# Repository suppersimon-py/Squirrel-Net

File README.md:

<div align="center">

  <h2>Squirrel-Core</h2>
  <h2>NOT FINISHED</h2>
  <p>
    <strong>SquirrelCore</strong> is an open-source PCB built around the <strong>ESP32-S3</strong> and <strong>SX1262</strong>.
    It is designed for long-range mesh networking using the open-source 
    <a href="https://meshtastic.org" target="_blank" rel="noopener noreferrer">Meshtastic</a> firmware.
    It can function as a client, node, or repeater in a distributed network.
  </p>
</div>

  <p>
    I wanted to design this as a challenge and a learning expirence on radio circuity for some time now, but without the funding (I'm kinda broke rn) this idea of mine wouldn't come to reality.
  </p>
  <h3>Continuing the development process</h3>
  <p>
    My plans are to not just stop on the PCB design but to also design a case around it. I am a visual modeler, I can't start work on the case until i have it in hand and can mesure and test fit,
    But I can assure I do have intresting design ideas for it. 
  </p>
  <p>
    Currently I have a github workflow that will automatically update, build, and release new versions of the meshtaic firmware to the realses page.
  </p>
  <p>
    I also need to fix somethings and test the actual firmware firmware.
  </p>

<div align="left">
  <h3>Features</h3>
  <ul>
    <li>ESP32-S3 microcontroller</li>
    <li>8MB Flash memory</li>
    <li>LoRaWAN, Wi-Fi, Bluetooth, and USB-C serial connectivity</li>
    <li>Adjustable battery charging: 400 mA or 1 A</li>
    <li>OLED display</li>
    <li>BME280 sensor (temperature, humidity, pressure)</li>
    <li>GPS module</li>
  </ul>
</div>

<div align="center">
  <h3>Meshtastic Links</h3>
  <p>
    <a href="https://meshtastic.org" style="text-decoration:none; font-weight:bold;">Get Started</a><br/>
    - <a href="https://meshtastic.org/docs/development/firmware/build">Building Instructions</a> – Learn how to compile the firmware from source.<br/>
    - <a href="https://meshtastic.org/docs/getting-started/flashing-firmware/esp32/">Flashing Instructions</a> – Install or update the firmware on your device.
  </p>
</div>

<div align="center">
  <h3>Licensing</h3>
</div>

<div align="left">
  <ul>
    <li>The core Meshtastic firmware in <code>/firmware/meshtastic</code> remains under its original license (as provided by the Meshtastic project).</li>
    <li>The SquirrelCore variant files in <code>/firmware/meshtastic/variants</code> are MIT-licensed (Copyright 2025 Supper Simon).</li>
    <li>When updating the repository, the variant is copied into Meshtastic, but the original Meshtastic license still applies to its code.</li>
  </ul>
</div>

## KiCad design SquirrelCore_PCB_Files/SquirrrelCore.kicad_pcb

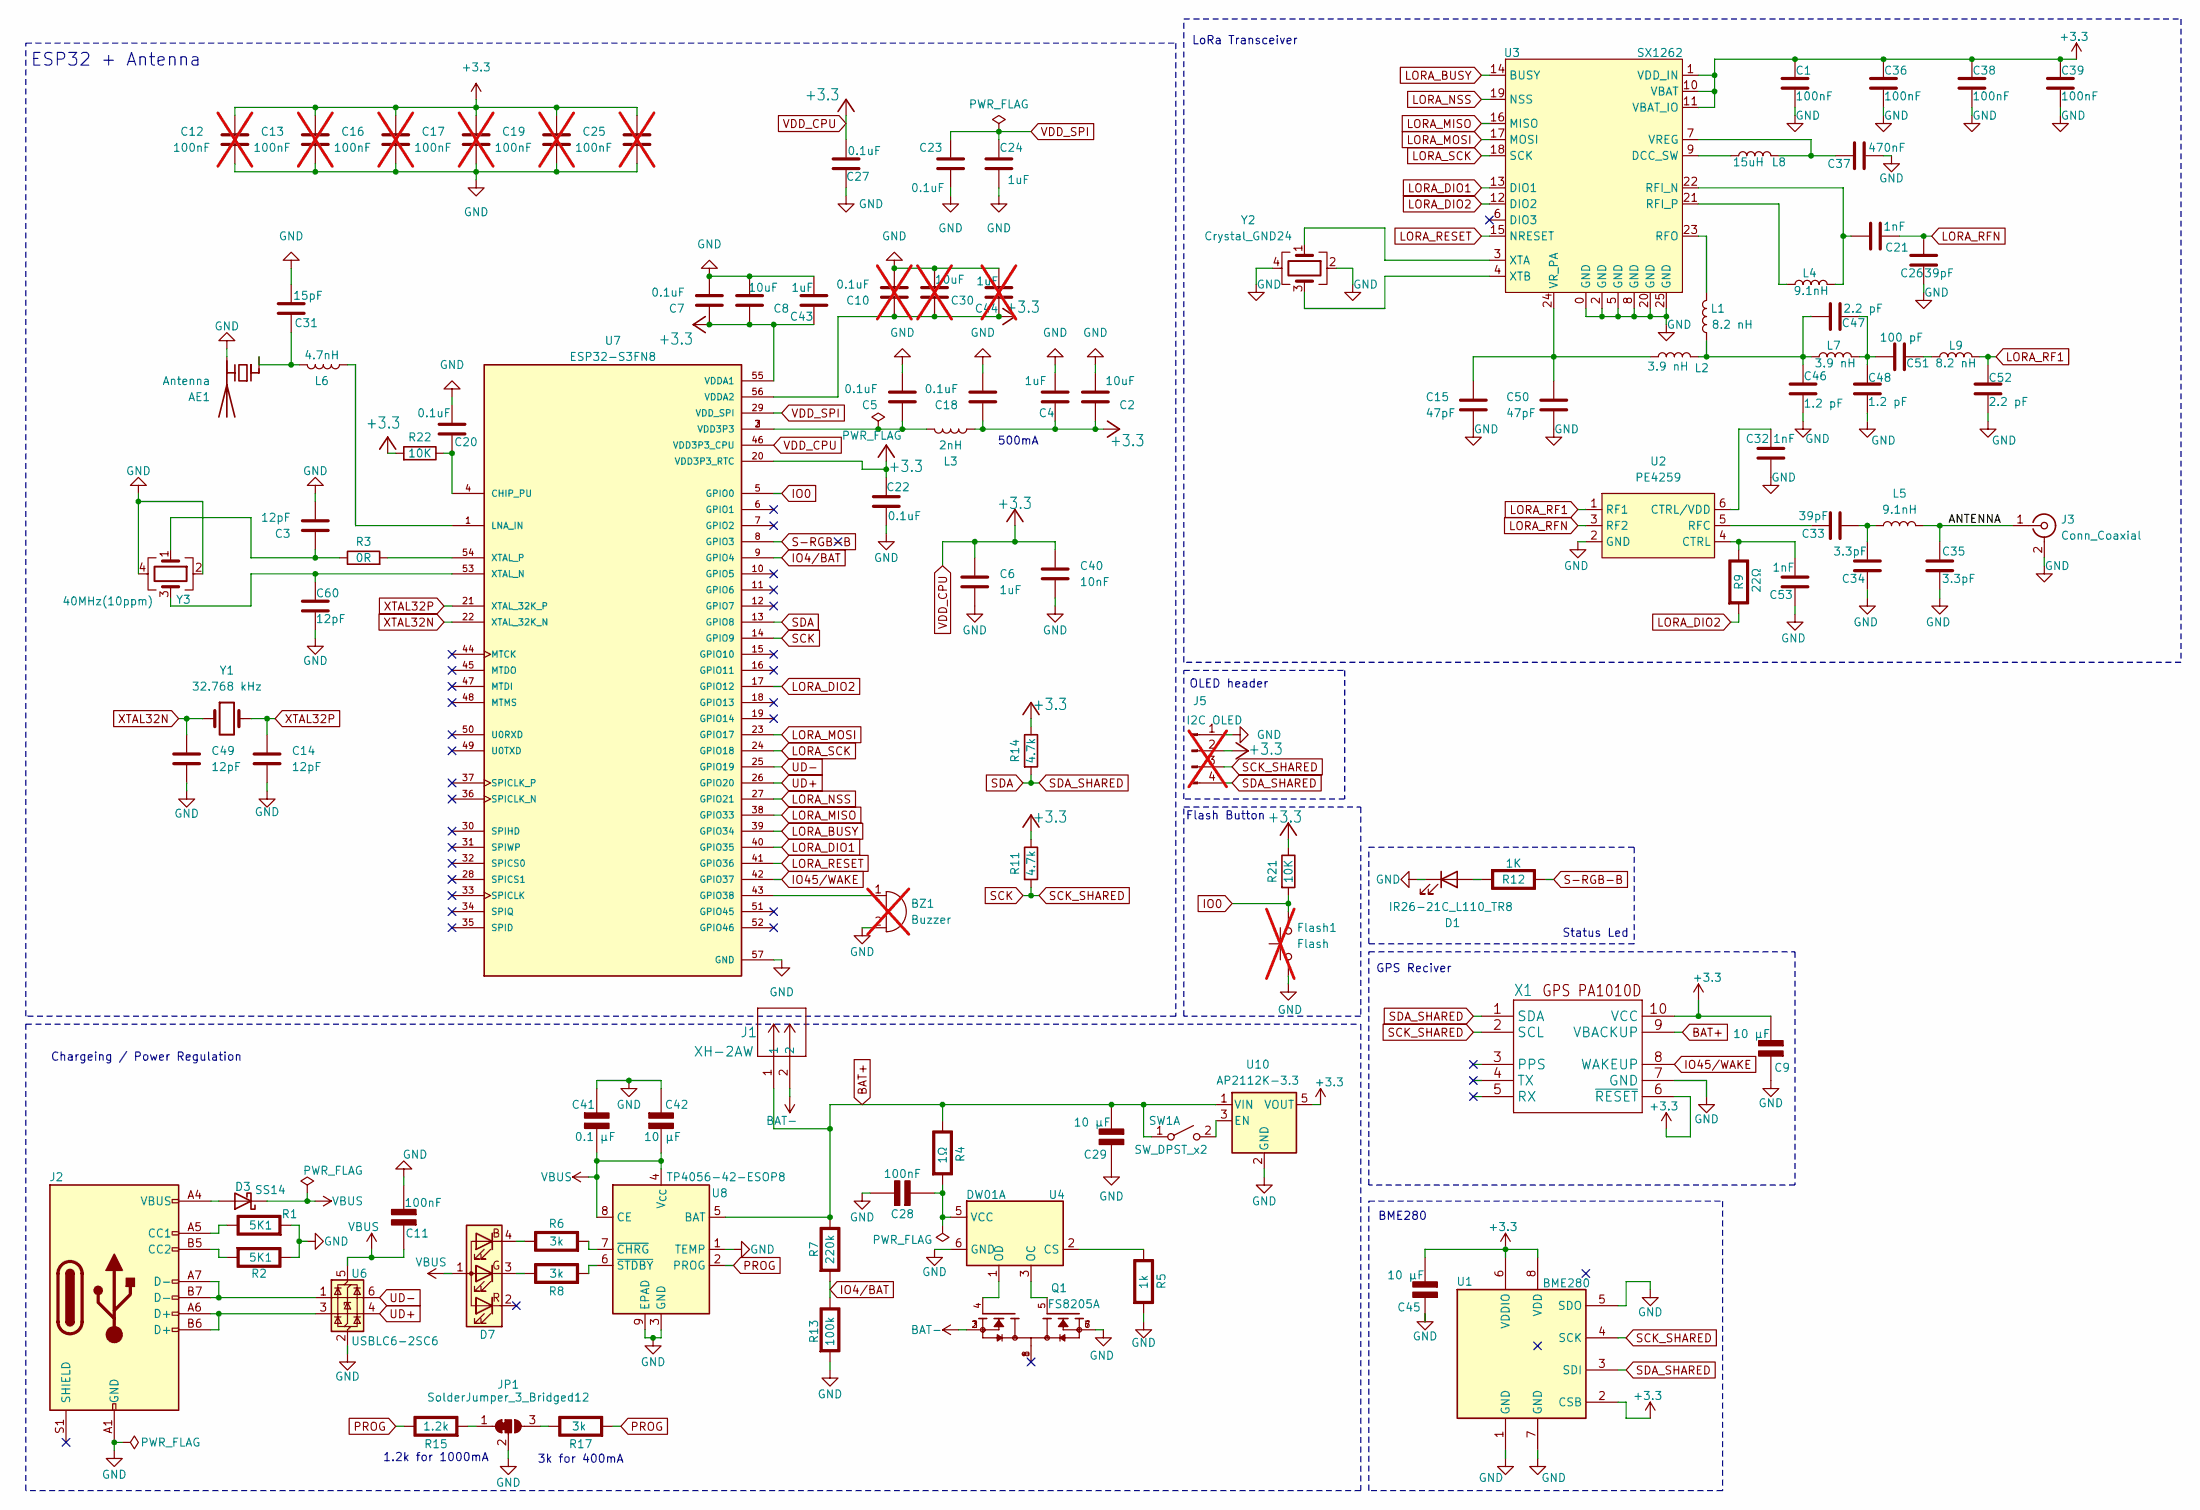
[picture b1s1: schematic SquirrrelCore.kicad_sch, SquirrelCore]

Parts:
AE1: Antenna; Texas_SWRA117D_2.4GHz_Left
BZ1: Buzzer; Buzzer_CUI_CPT-9019S-SMT; LCSC C95163; not fitted
C1, C36, C38, C39: 100nF; C_0402_1005Metric; LCSC C1525
C2, C8: 10uF; C_0402_1005Metric; MNF PART NUMBER C15525; LCSC C15525
C3, C14, C49, C60: 12pF; C_0402_1005Metric; MNF PART NUMBER C1547; LCSC C1547
C4, C6, C24, C43: 1uF; C_0402_1005Metric; MNF PART NUMBER C52923; LCSC C52923
C5, C7, C18, C20, C22, C23, C27: 0.1uF; C_0402_1005Metric; MNF PART NUMBER C1525; LCSC C1525
C9, C29, C42, C45: 10 µF; C_0402_1005Metric; Rating V; LCSC C15525
C10: 0.1uF; C_0402_1005Metric; MNF PART NUMBER C1525; LCSC C1525; not fitted
C11: 100nF; C_0402_1005Metric; Rating V; LCSC C307331
C12, C13, C16, C17, C19, C25: 100nF; C_0201_0603Metric; LCSC C49062; not fitted
C15, C50: 47pF; C_0402_1005Metric; LCSC C1567
C21: 1nF; C_0402_1005Metric; LCSC C1623
C26: 39pF; C_0402_1005Metric; LCSC C1623
C28: 100nF; C_0402_1005Metric; Rating V; LCSC C1525
C30: 10uF; C_0402_1005Metric; MNF PART NUMBER C15525; LCSC C15525; not fitted
C31: 15pF; C_0402_1005Metric; MNF PART NUMBER C1548; LCSC C1548
C32: 1nF; C_0402_1005Metric; LCSC C1523
C33: 39pF; C_0402_1005Metric; LCSC C1563
C34, C35: 3.3pF; C_0402_1005Metric; LCSC C1565
C37: 470nF; C_0402_1005Metric; LCSC C1623
C40: 10nF; C_0402_1005Metric; MNF PART NUMBER C15195; LCSC C15195
C41: 0.1 µF; C_0402_1005Metric; Rating V; LCSC C1525
C44: 1uF; C_0402_1005Metric; MNF PART NUMBER C52923; LCSC C52923; not fitted
C46, C48: 1.2 pF; C_0402_1005Metric; LCSC C1623
C47, C52: 2.2 pF; C_0402_1005Metric; LCSC C1623
C51: 100 pF; C_0402_1005Metric; LCSC C1623
C53: 1nF; C_0402_1005Metric; LCSC C1565
D1: IR26-21C_L110_TR8; LED_1206_3216Metric; LCSC C73929
D3: SS14; D_SMA; LCSC C2480
D7: LED_A_RGB; LED_RGB_Wuerth_150080M153000; LCSC C6785001
Flash1: Flash; SW_SPST_TS-1088-xR020; MNF PART NUMBER C318884; LCSC C318884; not fitted
J1: XH-2AW; CONN_XH-2AW_HRO; LCSC C157932
J2: USB_C_Receptacle_USB2.0_14P; USB_C_Receptacle_HCTL_HC-TYPE-C-16P-01A; LCSC C2894897
J3: Conn_Coaxial; IPEX-SMD_BWIPX-1-001E; LCSC C411563
J5: I2C OLED; PinHeader_1x04_P2.54mm_Vertical; LCSC C5248081; not fitted
JP1: SolderJumper_3_Bridged12; SolderJumper-3_P1.3mm_Bridged2Bar12_Pad1.0x1.5mm
L1, L9: 8.2 nH; L_0402_1005Metric; LCSC C3221788
L2, L7: 3.9 nH; L_0402_1005Metric; LCSC C3221788
L3: 2nH; L_0402_1005Metric; MNF PART NUMBER C77103; LCSC C77103
L4: 9.1nH; L_0402_1005Metric; LCSC C3221788
L5: 9.1nH; L_0402_1005Metric; LCSC C74297
L6: 4.7nH; L_0402_1005Metric; MNF PART NUMBER C13595; LCSC C13595
L8: 15uH; L_0402_1005Metric; LCSC C3221788
Q1: FS8205A; SOT-23-6; PARTREV 1.7; LCSC C908265
R1, R2: 5K1; C_0603; Rating W; LCSC C14677
R3: 0R; R_0402_1005Metric; MNF PART NUMBER C17168; LCSC C17168
R4: 1Ω; R_0402; Rating W; LCSC C25147
R5: 1k; R_0402; Rating W; LCSC C11702
R6, R8, R17: 3k; R_0402; Rating W; LCSC C25559
R7: 220k; R_0402; Rating W; LCSC C25546
R9: 22Ω; C_0402; Rating W; LCSC C861188
R11, R14: 4.7k; R_0402; MNF PART NUMBER C25744; LCSC C25744
R12: 1K; C_0603; Rating W; LCSC C861188
R13: 100k; R_0402; Rating W; LCSC C25741
R15: 1.2k; R_0402; Rating W; LCSC C25862
R21, R22: 10K; R_0402_1005Metric; MNF PART NUMBER C25744; LCSC C25744
SW1: SW_DPST_x2; SW_SPDT_CK_JS102011SAQN; LCSC C221660
U1: BME280; Bosch_LGA-8_2.5x2.5mm_P0.65mm_ClockwisePinNumbering; LCSC C92489
U2: PE4259; SOT65P215X110-6N; LCSC C47117600
U3: SX1262; QFN-24-1EP_4x4mm_P0.5mm_EP2.6x2.6mm; LCSC C191341
U4: DW01A; SOT-23-6; LCSC C351410
U6: USBLC6-2SC6; SOT-23-6; LCSC C7519
U7: ESP32-S3FN8; QFN40P700X700X90-57N; LCSC C2913196
U8: TP4056-42-ESOP8; SOIC-8-1EP_3.9x4.9mm_P1.27mm_EP2.41x3.3mm_ThermalVias; LCSC C16581
U10: AP2112K-3.3; SOT-23-5; LCSC C23380830
X1: GPS_PA1010D; LCSC C9900050424
Y1: 32.768 kHz; Crystal_SMD_3215-2Pin_3.2x1.5mm; MNF PART NUMBER C32346; LCSC C32346
Y2: Crystal_GND24; Crystal_SMD_3225-4Pin_3.2x2.5mm; LCSC C9900039190
Y3: 40MHz(10ppm); Crystal_SMD_2520-4Pin_2.5x2.0mm; MNF PART NUMBER C5261125; LCSC C5261125

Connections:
/ANTENNA: C35.1, J3.1 (In), L5.2
BAT+: C29.2 (-), J1.1, R4.1 (+), R7.1 (+), SW1.1 (A), U8.5 (BAT), U10.1 (VIN), X1.9 (VBACKUP)
BAT-: J1.2, Q1.2, Q1.3
GND: AE1.2 (PCB_Trace), BZ1.2 (-), C1.2, C2.2, C3.2, C4.2, C5.2, C6.2, C7.2, C8.2, C9.1 (+), C10.2, C11.2 (-), C12.2, C13.2, C14.2, C15.1, C16.2, C17.2, C18.2, C19.2, C20.2, C22.2, C23.2, C24.2, C25.2, C26.2, C27.2, C28.1 (+), C29.1 (+), C30.2, C31.2, C32.2, C34.1, C35.2, C36.2, C37.2, C38.2, C39.2, C40.2, C41.1 (+), C42.1 (+), C43.2, C44.2, C45.1 (+), C46.2, C48.2, C49.2, C50.1, C52.2, C53.1, C60.1, D1.1 (K), Flash1.1, J2.A1 (GND), J2.A12 (GND), J2.B1 (GND), J2.B12 (GND), J3.2 (Ext), J5.1, JP1.2 (C), Q1.6, Q1.7, R1.2 (-), R2.1 (+), R5.2 (-), R13.2 (-), U1.1 (GND), U1.5 (SDO), U1.7 (GND), U2.2 (GND), U3.0 (GND), U3.2 (GND), U3.5 (GND), U3.8 (GND), U3.20 (GND), U3.25 (GND), U4.6 (GND), U6.2 (GND), U7.57 (GND), U8.1 (TEMP), U8.3 (GND), U8.9 (EPAD), U10.2 (GND), X1.7 (GND), Y2.2, Y2.4, Y3.2, Y3.4
IO0: Flash1.2, R21.2, U7.5 (GPIO0)
IO4/BAT: R7.2 (-), R13.1 (+), U7.9 (GPIO4)
IO45/WAKE: U7.42 (GPIO37), X1.8 (WAKEUP)
LORA_BUSY: U3.14 (BUSY), U7.39 (GPIO34)
LORA_DIO1: U3.13 (DIO1), U7.40 (GPIO35)
LORA_DIO2: R9.2 (-), U3.12 (DIO2), U7.17 (GPIO12)
LORA_MISO: U3.16 (MISO), U7.38 (GPIO33)
LORA_MOSI: U3.17 (MOSI), U7.23 (GPIO17)
LORA_NSS: U3.19 (NSS), U7.27 (GPIO21)
LORA_RESET: U3.15 (NRESET), U7.41 (GPIO36)
LORA_RF1: C52.1, L9.2, U2.1 (RF1)
LORA_RFN: C21.2, C26.1, U2.3 (RF2)
LORA_SCK: U3.18 (SCK), U7.24 (GPIO18)
unnamed: AE1.1 (FEED), C31.1, L6.2
unnamed: BZ1.1 (+), U7.43 (GPIO38)
unnamed: C3.1, R3.1, Y3.1
unnamed: C5.1, L3.2, U7.2 (VDD3P3), U7.3 (VDD3P3)
unnamed: C28.2 (-), R4.2 (-), U4.5 (VCC)
unnamed: C33.2, C34.2, L5.1
unnamed: C46.1, C47.1, L1.1, L2.2, L7.1
unnamed: C47.2, C48.1, C51.1, L7.2
unnamed: C51.2, L9.1
unnamed: D1.2 (A), R12.2 (-)
unnamed: D3.2 (A), J2.A4 (VBUS), J2.A9 (VBUS), J2.B4 (VBUS), J2.B9 (VBUS)
unnamed: D7.4 (BA), R6.1 (+)
unnamed: D7.3 (GA), R8.1 (+)
unnamed: J2.A5 (CC1), R1.1 (+)
unnamed: J2.B5 (CC2), R2.2 (-)
unnamed: J2.A6 (D+), J2.B6 (D+), U6.3 (I/O2)
unnamed: J2.A7 (D-), J2.B7 (D-), U6.1 (I/O1)
unnamed: JP1.1 (A), R15.2 (-)
unnamed: JP1.3 (B), R17.1 (+)
unnamed: R5.1 (+), U4.2 (CS)
unnamed: R6.2 (-), U8.7 (~CHRG)
unnamed: R8.2 (-), U8.6 (~STDBY)
unnamed: C53.2, R9.1 (+), U2.4 (CTRL)
unnamed: SW1.2 (B), U10.3 (EN)
unnamed: C32.1, U2.6 (CTRL/VDD)
unnamed: C33.1, U2.5 (RFC)
unnamed: L8.1, U3.9 (DCC_SW)
unnamed: C21.1, L4.2, U3.22 (RFI_N)
unnamed: L4.1, U3.21 (RFI_P)
unnamed: L1.2, U3.23 (RFO)
unnamed: C37.1, L8.2, U3.7 (VREG)
unnamed: C15.2, C50.2, L2.1, U3.24 (VR_PA)
unnamed: U3.3 (XTA), Y2.1
unnamed: U3.4 (XTB), Y2.3
unnamed: Q1.5, U4.3 (OC)
unnamed: Q1.4, U4.1 (OD)
unnamed: C20.1, R22.1, U7.4 (CHIP_PU)
unnamed: L6.1, U7.1 (LNA_IN)
unnamed: C60.2, U7.53 (XTAL_N), Y3.3
unnamed: R3.2, U7.54 (XTAL_P)
PROG: R15.1 (+), R17.2 (-), U8.2 (PROG)
S-RGB-B: R12.1 (+), U7.8 (GPIO3)
SCK: J5.3, R11.2, U1.4 (SCK), U7.14 (GPIO9), X1.2 (SCL)
SDA: J5.4, R14.2, U1.3 (SDI), U7.13 (GPIO8), X1.1 (SDA)
UD+: U6.4 (I/O2), U7.26 (GPIO20)
UD-: U6.6 (I/O1), U7.25 (GPIO19)
VBUS: C11.1 (+), C41.2 (-), C42.2 (-), D3.1 (K), D7.1 (K), U6.5 (VBUS), U8.4 (V_{CC}), U8.8 (CE)
VDD_CPU: C1.1, C2.1, C4.1, C6.1, C7.1, C8.1, C9.2 (-), C10.1, C12.1, C13.1, C16.1, C17.1, C18.1, C19.1, C22.1, C25.1, C27.1, C30.1, C36.1, C38.1, C39.1, C40.1, C43.1, C44.1, C45.2 (-), J5.2, L3.1, R11.1, R14.1, R21.1, R22.2, U1.2 (CSB), U1.6 (VDDIO), U1.8 (VDD), U3.1 (VDD_IN), U3.10 (VBAT), U3.11 (VBAT_IO), U7.20 (VDD3P3_RTC), U7.46 (VDD3P3_CPU), U7.55 (VDDA1), U7.56 (VDDA2), U10.5 (VOUT), X1.6 (~RESET), X1.10 (VCC)
VDD_SPI: C23.1, C24.1, U7.29 (VDD_SPI)
XTAL32N: C49.1, U7.22 (XTAL_32K_N), Y1.1
XTAL32P: C14.1, U7.21 (XTAL_32K_P), Y1.2

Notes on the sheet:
Flash Button
Status Led
1.2k for 1000mA
3k for 400mA
ESP32 + Antenna
LoRa Transceiver
OLED header
GPS Reciver
Chargeing / Power Regulation
BME280
500mA

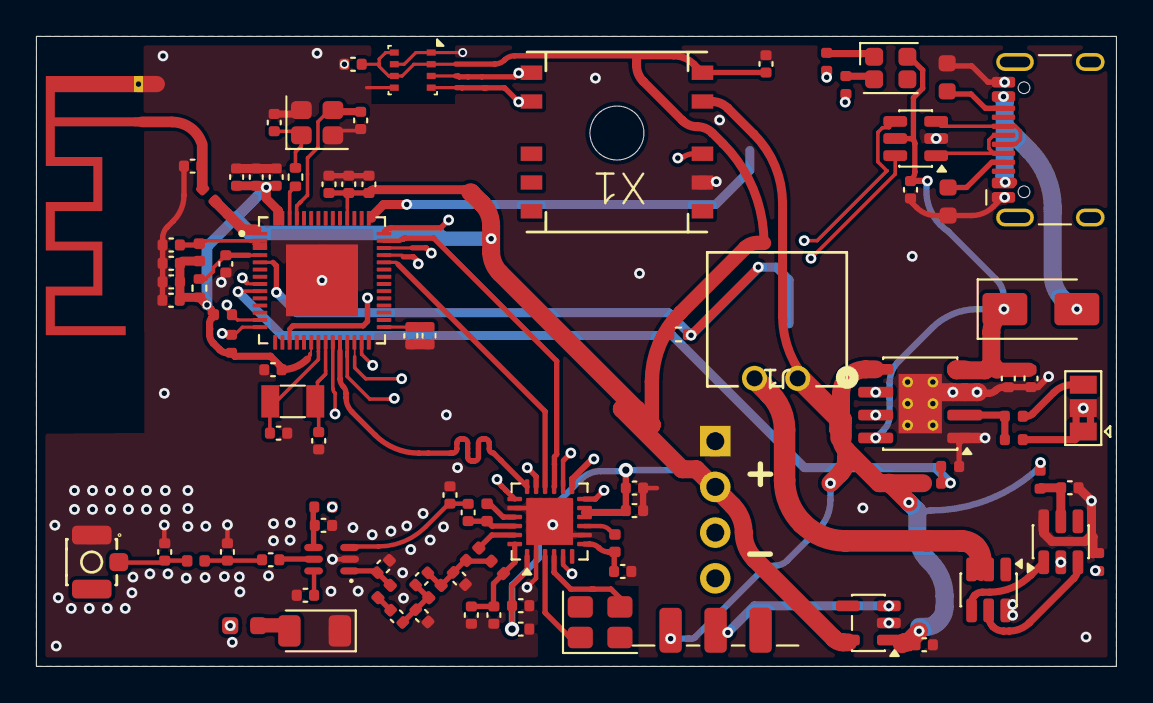
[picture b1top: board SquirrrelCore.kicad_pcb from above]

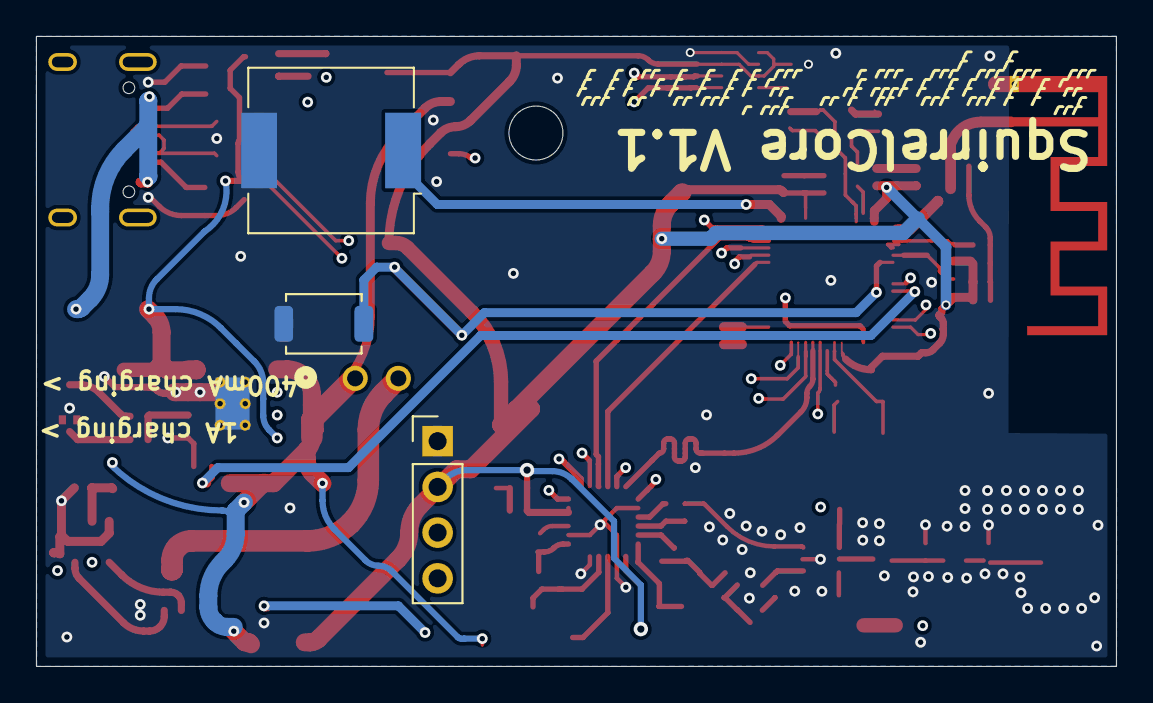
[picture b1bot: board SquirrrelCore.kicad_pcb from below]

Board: 4 copper layers, 60.0 x 35.0 mm, 97 parts (4 on the bottom side), 68 nets.

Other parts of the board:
svg2mod: G***; logo_F-SilkS

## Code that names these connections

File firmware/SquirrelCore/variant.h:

#pragma once

// =========================================================
// SquirrelCore Variant Definition
// Hardware: ESP32-S3FN8 + SX1262 + PA1010D + BME280 + OLED (HS91L02W2C01)
// =========================================================

// -------------------- Board Identification --------------------
#define VENDOR_CUSTOM
#define BOARD_SQUIRRELCORE
#define BOARD_NAME                  "SquirrelCore"
#define HAS_LORA
#define HAS_BME280
#define HAS_GPS
#define HAS_DISPLAY
#define HAS_BUZZER
#define HAS_BATTERY_MONITOR

// -------------------- I2C Bus --------------------
#define I2C_SDA                     8
#define I2C_SCL                     9

// Shared bus devices (different I2C addresses):
//  - BME280:    0x76 or 0x77
//  - GPS (PA1010D): 0x10 (default, depends on config)
//  - OLED (HS91L02W2C01): 0x3C (typical)

// -------------------- LoRa (SX1262) --------------------
#define LORA_SCK                    18
#define LORA_MISO                   33
#define LORA_MOSI                   17
#define LORA_NSS                    21
#define LORA_RESET                  36
#define LORA_DIO1                   35
#define LORA_BUSY                   34
// DIO0 not required for SX1262, only DIO1 used for IRQ

// -------------------- GPS (PA1010D) --------------------
#define GPS_SDA                     I2C_SDA
#define GPS_SCL                     I2C_SCL
#define GPS_RESET                   -1     // Tied to 3.3V
#define GPS_WAKE                    37
#define GPS_POWER_EN                -1     // Always powered

// -------------------- Sensors --------------------
#define BME280_SDA                  I2C_SDA
#define BME280_SCL                  I2C_SCL

// -------------------- Display --------------------
#define OLED_SDA                    I2C_SDA
#define OLED_SCL                    I2C_SCL
#define OLED_ADDR                   0x3C

// -------------------- Battery Sense --------------------
#define BATTERY_SENSE_PIN           4
#define BATTERY_DIVIDER_HIGH        220000.0f  // 220kΩ
#define BATTERY_DIVIDER_LOW         100000.0f  // 100kΩ
#define BATTERY_VREF                3.3f
// Voltage divider output = Vbat * (Rlow / (Rhigh + Rlow))

// -------------------- Indicators --------------------
#define LED_PIN                     14
#define LED_ACTIVE_LEVEL            HIGH

// -------------------- Buzzer --------------------
#define BUZZER_PIN                  38
#define BUZZER_ACTIVE_LEVEL         HIGH

// -------------------- Helper Macros --------------------
#define UNUSED_PIN                  (-1)

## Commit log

2025-10-20 Auto-update Meshtastic to v2.6.11.60ec05e
2025-10-20 Update update-meshtastic.yml
    Added auto build for Squirrel Core variant
2025-10-20 Added SupperSimonLogo.png
2025-10-20 Update LICENSE
2025-10-24 Added the bill of materials
2025-10-29 Create te
2025-10-29 Rename SquirrrelNet.pdf to SquirrrelCore.pdf
2025-10-29 Rename SquirrrelNet.svg to SquirrrelCore.svg
2025-10-29 Create t
2025-10-30 Added gif
